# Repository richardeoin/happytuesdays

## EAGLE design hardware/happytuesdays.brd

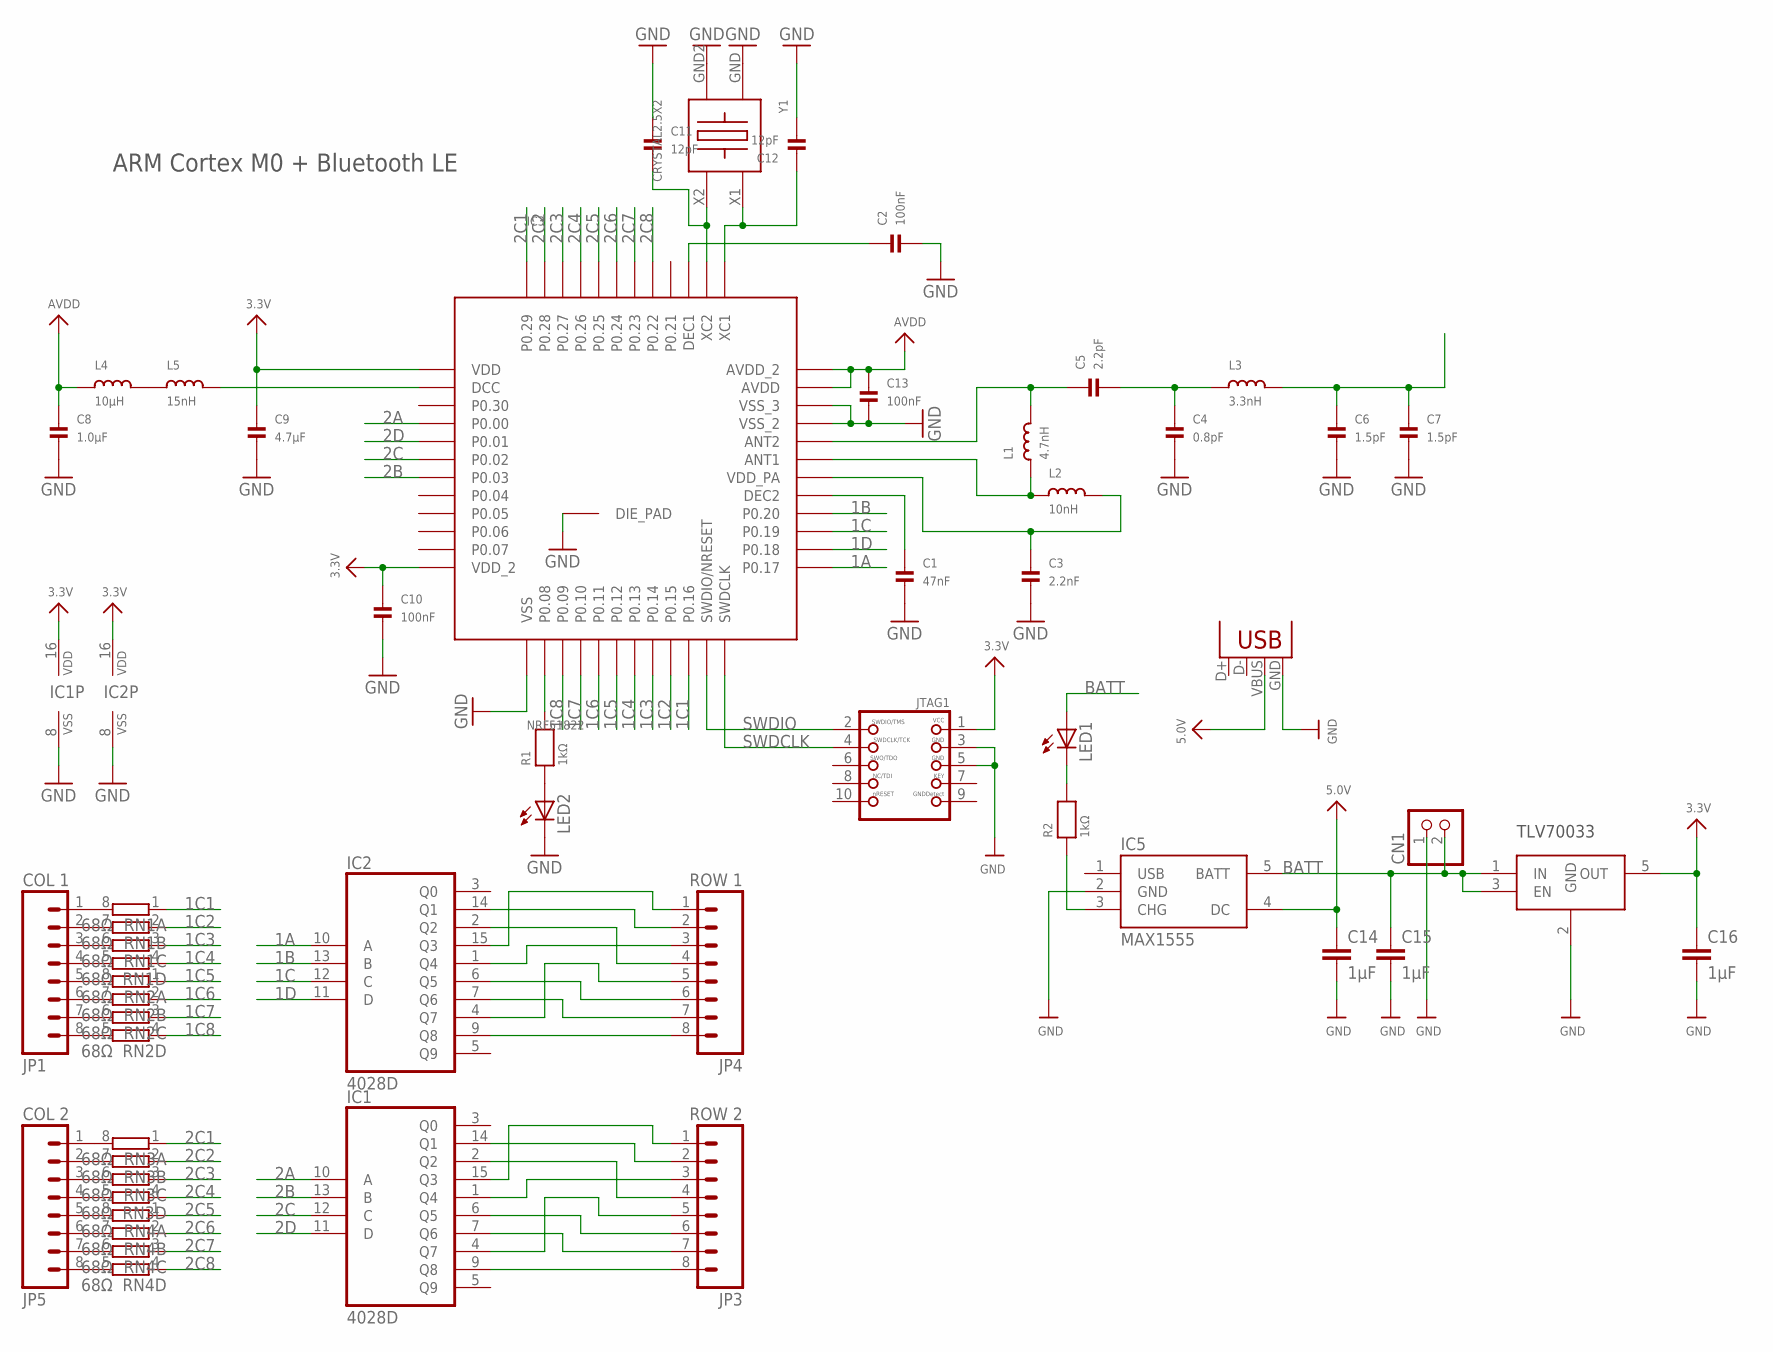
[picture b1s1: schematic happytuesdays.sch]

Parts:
C1: 47nF; _0402
C2, C10, C13: 100nF; _0402
C3: 2.2nF; _0402
C4: 0.8pF; _0402
C5: 2.2pF; _0402
C6, C7: 1.5pF; _0402
C8: 1.0µF; _0402
C9: 4.7µF; _0402
C11, C12: 12pF; _0402
C14, C15, C16: 1µF; C0603K
CN1: JST_2PIN; JSTPH2
IC1, IC2: 4028D; SO16
IC3: NRF51822; QFN48
IC4: TLV70033DCK; SC70-5L
IC5: MAX1555; SOT23-5
JP1: COL 1; 1X08_LOCK
JP3: ROW 2; 1X08_LOCK
JP4: ROW 1; 1X08_LOCK
JP5: COL 2; 1X08_LOCK
JTAG1: JTAG-CORTEXM3SMT; 2X05_1.27MM_SMT
L1: 4.7nH; _0402
L2: 10nH; _0402
L3: 3.3nH; _0402
L4: 10µH; _0402
L5: 15nH; _0402
LED1, LED2: LEDCHIPLED_0603; CHIPLED_0603
R1, R2: 1kΩ; _0402
RN1, RN2, RN3, RN4: 68Ω; 4X0402ARV341
X1: USB-MICROB
Y1: CRYSTAL2.5X2; 2.5X2MM

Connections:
1A: IC2.10 (A), IC3.25 (P0.17)
1B: IC2.13 (B), IC3.28 (P0.20)
1C: IC2.12 (C), IC3.27 (P0.19)
1C1: IC3.22 (P0.16), RN1.1
1C1R: JP1.1, RN1.8 (2)
1C2: IC3.21 (P0.15), RN1.2 (1)
1C2R: JP1.2, RN1.7 (2)
1C3: IC3.20 (P0.14), RN1.3 (1)
1C3R: JP1.3, RN1.6 (2)
1C4: IC3.19 (P0.13), RN1.4 (1)
1C4R: JP1.4, RN1.5 (2)
1C5: IC3.18 (P0.12), RN2.1
1C5R: JP1.5, RN2.8 (2)
1C6: IC3.17 (P0.11), RN2.2 (1)
1C6R: JP1.6, RN2.7 (2)
1C7: IC3.16 (P0.10), RN2.3 (1)
1C7R: JP1.7, RN2.6 (2)
1C8: IC3.15 (P0.09), RN2.4 (1)
1C8R: JP1.8, RN2.5 (2)
1D: IC2.11 (D), IC3.26 (P0.18)
1Q1: IC2.14 (Q1), JP4.2
1Q2: IC2.2 (Q2), JP4.4
1Q3: IC2.15 (Q3), JP4.1
1Q4: IC2.1 (Q4), JP4.3
1Q5: IC2.6 (Q5), JP4.6
1Q6: IC2.7 (Q6), JP4.7
1Q7: IC2.4 (Q7), JP4.5
1Q8: IC2.9 (Q8), JP4.8
2A: IC1.10 (A), IC3.4 (P0.00)
2B: IC1.13 (B), IC3.7 (P0.03)
2C: IC1.12 (C), IC3.6 (P0.02)
2C1: IC3.48 (P0.29), RN3.1
2C1R: JP5.1, RN3.8 (2)
2C2: IC3.47 (P0.28), RN3.2 (1)
2C2R: JP5.2, RN3.7 (2)
2C3: IC3.46 (P0.27), RN3.3 (1)
2C3R: JP5.3, RN3.6 (2)
2C4: IC3.45 (P0.26), RN3.4 (1)
2C4R: JP5.4, RN3.5 (2)
2C5: IC3.44 (P0.25), RN4.1
2C5R: JP5.5, RN4.8 (2)
2C6: IC3.43 (P0.24), RN4.2 (1)
2C6R: JP5.6, RN4.7 (2)
2C7: IC3.42 (P0.23), RN4.3 (1)
2C7R: JP5.7, RN4.6 (2)
2C8: IC3.41 (P0.22), RN4.4 (1)
2C8R: JP5.8, RN4.5 (2)
2D: IC1.11 (D), IC3.5 (P0.01)
2Q1: IC1.14 (Q1), JP3.2
2Q2: IC1.2 (Q2), JP3.4
2Q3: IC1.15 (Q3), JP3.1
2Q4: IC1.1 (Q4), JP3.3
2Q5: IC1.6 (Q5), JP3.6
2Q6: IC1.7 (Q6), JP3.7
2Q7: IC1.4 (Q7), JP3.5
2Q8: IC1.9 (Q8), JP3.8
3.3V: C9.1, C10.1, C16.1, IC1.16 (VDD), IC2.16 (VDD), IC3.1 (VDD), IC3.12 (VDD_2), IC4.5 (OUT), JTAG1.1
5.0V: C14.1, IC5.4 (DC), X1.VBUS
ANT: C6.1, C7.1, L3.2
ANT1: IC3.31 (ANT1), L1.1, L2.1
ANT2: C5.1, IC3.32 (ANT2), L1.2
AVDD: C8.1, C13.1, IC3.35 (AVDD), IC3.36 (AVDD_2), L4.1
BATT: C15.1, CN1.2, IC4.1 (IN), IC4.3 (EN), IC5.5 (BATT), LED1.A
CHG: IC5.3 (CHG), R2.1
DCC: IC3.2 (DCC), L5.2
DEC1: C2.1, IC3.39 (DEC1)
DEC2: C1.1, IC3.29 (DEC2)
GND: C1.2, C2.2, C3.2, C4.2, C6.2, C7.2, C8.2, C9.2, C10.2, C11.1, C12.2, C13.2, C14.2, C15.2, C16.2, CN1.1, IC1.8 (VSS), IC2.8 (VSS), IC3.13 (VSS), IC3.33 (VSS_2), IC3.34 (VSS_3), IC3.GND (DIE_PAD), IC4.2 (GND), IC5.2 (GND), JTAG1.3, JTAG1.5, LED2.C, X1.GND, Y1.GND, Y1.GND2
LED: LED1.C, R2.2
unnamed: L4.2, L5.1
unnamed: IC3.14 (P0.08), R1.2
unnamed: LED2.A, R1.1
SWDCLK: IC3.24 (SWDCLK), JTAG1.4
SWDIO: IC3.23 (SWDIO/NRESET), JTAG1.2
UNBAL: C4.1, C5.2, L3.1
VDD_PA: C3.1, IC3.30 (VDD_PA), L2.2
X1: C12.1, IC3.37 (XC1), Y1.X1
X2: C11.2, IC3.38 (XC2), Y1.X2

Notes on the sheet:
ARM Cortex M0 + Bluetooth LE
TLV70033

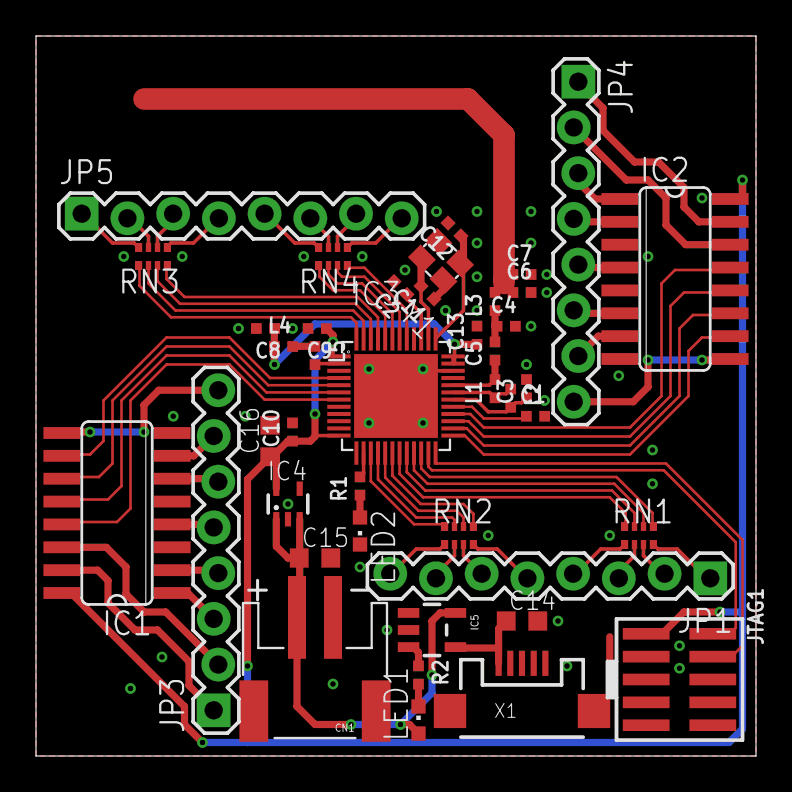
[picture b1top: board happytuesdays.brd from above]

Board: 2 copper layers, 40.0 x 40.0 mm, 42 parts (0 on the bottom side), 78 nets.

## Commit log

2014-10-12 Initial Commit, basic board design
2015-03-11 Board finished, added partslist
2015-03-13 Added partlist
2015-03-13 Added license
2015-03-13 Added mouser sources
2015-03-23 Start firmware
2015-03-23 Created subtree for nrf51
2015-03-23 Heart rate example
2015-03-23 Added L4, L5
2015-03-23 Fixed etags dependance generation, also fixed upstream in toolchain

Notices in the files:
parts and their libraries:
microbuilder_v3: This work is placed in the public domain, and may be freely used for commercial and non-commercial work with the following conditions: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
SparkFun: Licensing: CC v3.0 Share-Alike You are welcome to use this library for commercial purposes.
